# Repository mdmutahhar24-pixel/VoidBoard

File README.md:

# VoidBoard

Image of Casing

Image of VoidBoard Design

Image of VoidBoard Schematic

Image of VoidBoard PCB

Description: A macropad with 9 keys, 128x32 OLED, a rotary encoder. Based off the game: Hollow Knight.

Materials List:

| Part Item | Quantity |
|-----------|----------|
|Seeed XIAO RP2040 microcontroller| 1 |
|1N4148 through-hole diodes| 9 |
|MX-style mechanical switches| 9 |
|EC11 rotary encoders (20mm D-shaft)| 1 |
|0.91” 128×32 OLED display| 1 |
|Blank DSA keycaps| 9 |
|M3×16mm screws| 6 |
|M3×5×4mm heatset inserts| 6 |

Enter the bootloader in 3 ways:

* **Bootmagic reset**: Hold down the key at (0,0) in the matrix (usually the top left key or Escape) and plug in the keyboard
* **Physical reset button**: Briefly press the button on the back of the PCB - some may have pads you must short instead
* **Keycode in layout**: Press the key mapped to `QK_BOOT` if it is available

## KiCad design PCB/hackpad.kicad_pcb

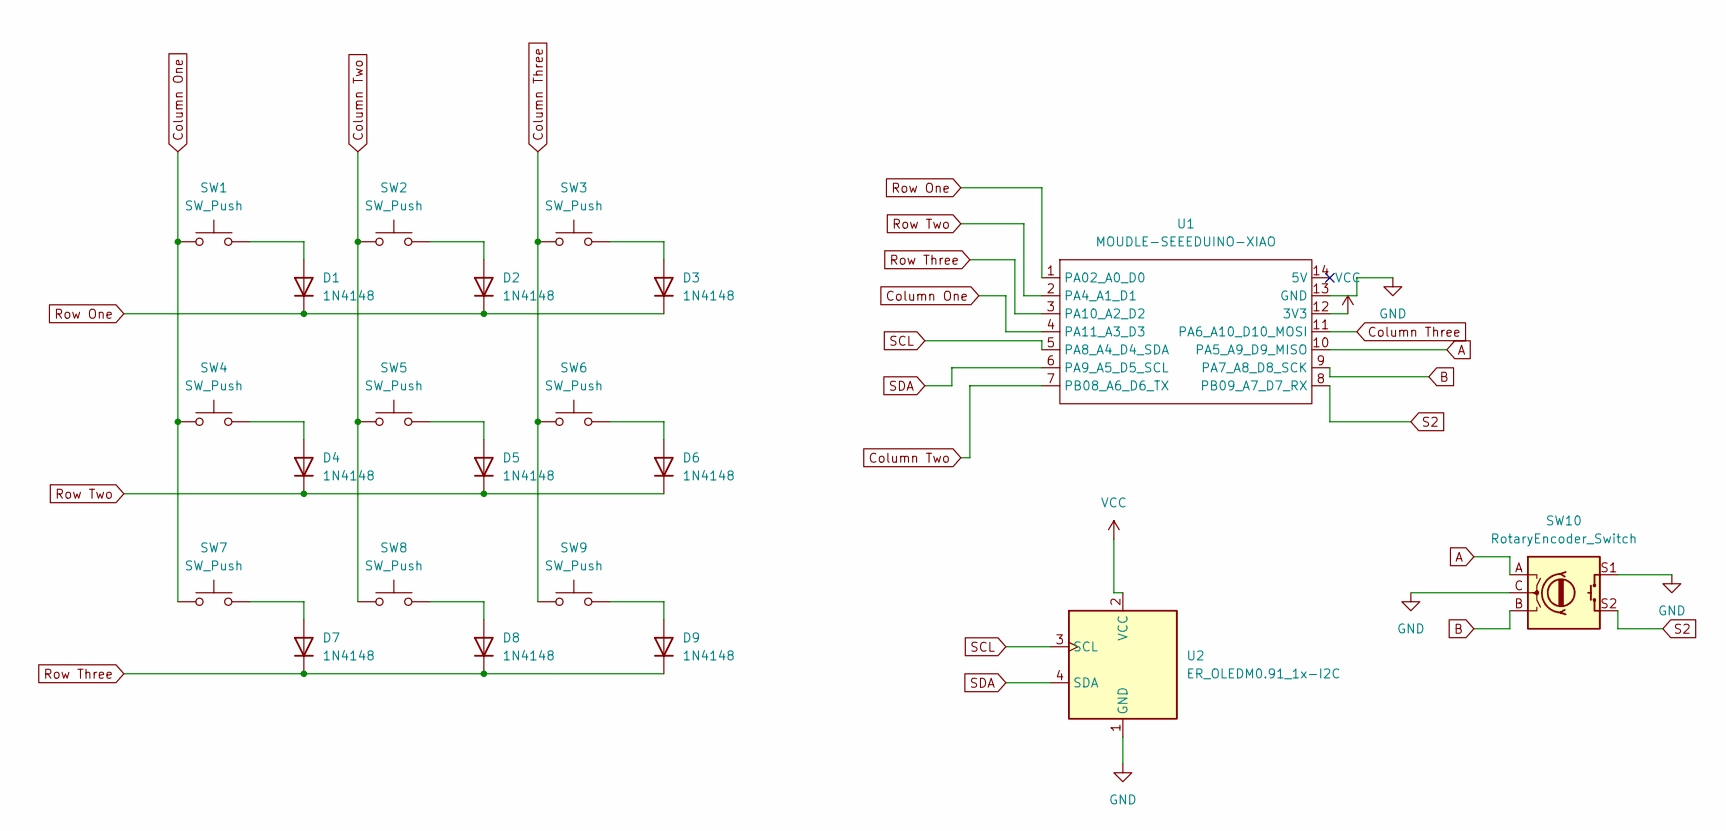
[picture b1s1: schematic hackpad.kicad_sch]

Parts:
D1, D2, D3, D4, D5, D6, D7, D8, D9: 1N4148; D_DO-35_SOD27_P7.62mm_Horizontal
SW1, SW2, SW3, SW4, SW5, SW6, SW7, SW8, SW9: SW_Push; SW_Cherry_MX_1.00u_PCB
SW10: RotaryEncoder_Switch; RotaryEncoder_Alps_EC11E-Switch_Vertical_H20mm
U1: MOUDLE-SEEEDUINO-XIAO; XIAO-Generic-Hybrid-14P-2.54-21X17.8MM
U2: ER_OLEDM0.91_1x-I2C

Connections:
A: SW10.A, U1.10 (PA5_A9_D9_MISO)
B: SW10.B, U1.9 (PA7_A8_D8_SCK)
Column One: SW1.1, SW4.1, SW7.1, U1.4 (PA11_A3_D3)
Column Three: SW3.1, SW6.1, SW9.1, U1.11 (PA6_A10_D10_MOSI)
Column Two: SW2.1, SW5.1, SW8.1, U1.7 (PB08_A6_D6_TX)
GND: SW10.C, SW10.S1, U1.13 (GND), U2.1 (GND)
unnamed: D1.2 (A), SW1.2
unnamed: D2.2 (A), SW2.2
unnamed: D3.2 (A), SW3.2
unnamed: D4.2 (A), SW4.2
unnamed: D5.2 (A), SW5.2
unnamed: D6.2 (A), SW6.2
unnamed: D7.2 (A), SW7.2
unnamed: D8.2 (A), SW8.2
unnamed: D9.2 (A), SW9.2
Row One: D1.1 (K), D2.1 (K), D3.1 (K), U1.1 (PA02_A0_D0)
Row Three: D7.1 (K), D8.1 (K), D9.1 (K), U1.3 (PA10_A2_D2)
Row Two: D4.1 (K), D5.1 (K), D6.1 (K), U1.2 (PA4_A1_D1)
S2: SW10.S2, U1.8 (PB09_A7_D7_RX)
SCL: U1.5 (PA8_A4_D4_SDA), U2.3 (SCL)
SDA: U1.6 (PA9_A5_D5_SCL), U2.4 (SDA)
VCC: U1.12 (3V3), U2.2 (VCC)

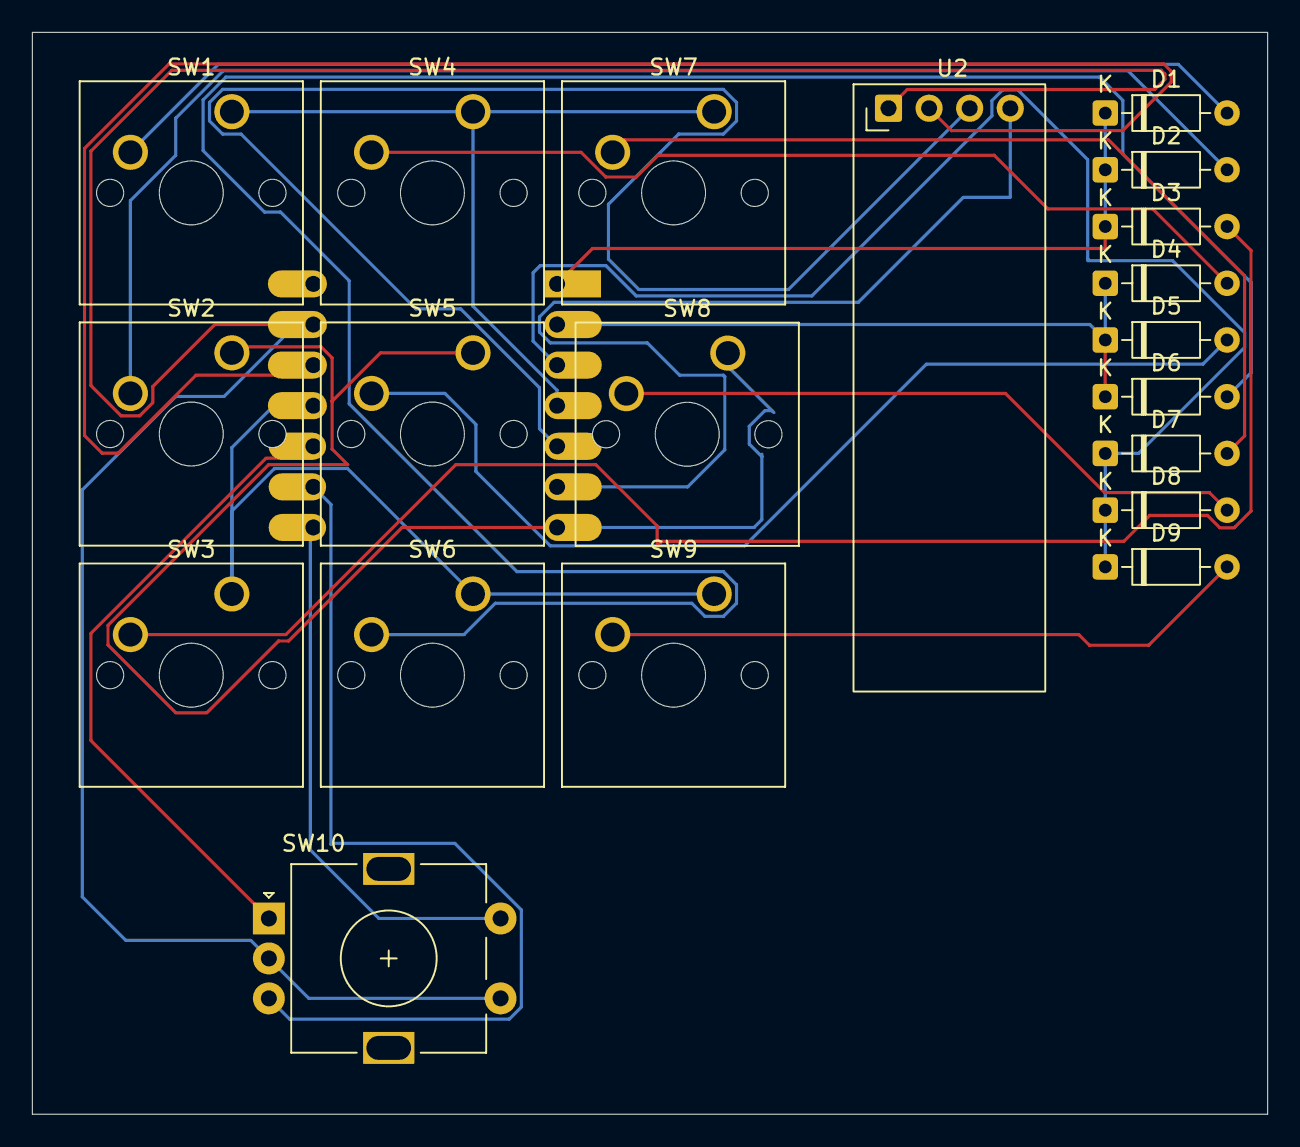
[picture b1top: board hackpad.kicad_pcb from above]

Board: 2 copper layers, 77.3 x 67.7 mm, 21 parts (1 on the bottom side), 22 nets.

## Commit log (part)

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2026-06-10 Create j
2026-06-10 assembly commit
2026-06-10 firmware stuff
2026-06-10 Bottom + top
2026-06-10 Rename animation.h to Firmware/animation.h
2026-06-10 Rename keyboard.json to Firmware/keyboard.json
2026-06-10 Rename readme.md to Firmware/readme.md
2026-06-10 Rename rules.mk to Firmware/rules.mk
2026-06-10 Rename voidboard.c to Firmware/voidboard.c
2026-06-10 Rename keymaps/default/keymap.c to Firmware/keymaps/default/keymap.c
2026-06-10 Replace screenshot with larger version
    Updated the screenshot in the README to a larger image.
2026-06-10 Added Gerbers
2026-06-10 Enhance README with VoidBoard images and details
    Added images and detailed description of VoidBoard design, schematic, and PCB along with a materials list.
